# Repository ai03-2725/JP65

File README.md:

# JP65  
65%配列疑似JISキーボードPCB  
65% JIS-like hotswap keyboard PCB

Features  
- MITライセンスのもとでソース公開 / Open-source under the MIT license  
- Kailh製ソケットで全キーホットスワップ可能、はんだ付け無しで組み立て可能 / Fully hotswap  
- TADA68対応の65％ケースで使用可能 / Compatible with TADA68 standard cases  
- 一般的なキーサイズのみの日本語入力配列なので、GMKやePBTなどの標準キーキャップセットを使用可能 / Features a JIS-like key layout using standard keycap sizes   

[配列データ / Layout data](http://www.keyboard-layout-editor.com/#/gists/1bc89d661a44315f9f2ad37c4e321d41)  

Notes  
- 一番左下のネジ位置は一部分Winキーと重なってしまうので、ケースによっては入らない可能性があります。その場合はネジ無しでもOKです。/ The bottom-left screw might not fit due to collision against switches; if it does not, leave the screw uninstalled.  
- 左Winキー用スイッチの脚の一本はケース側スペーサーの位置と重なってしまうので、フラッシュカットなどで切る必要があります。One PCB-mount switch leg may need to be trimmed on the left Win key to fit; it is triple-circled on the silkscreen layer for identification.

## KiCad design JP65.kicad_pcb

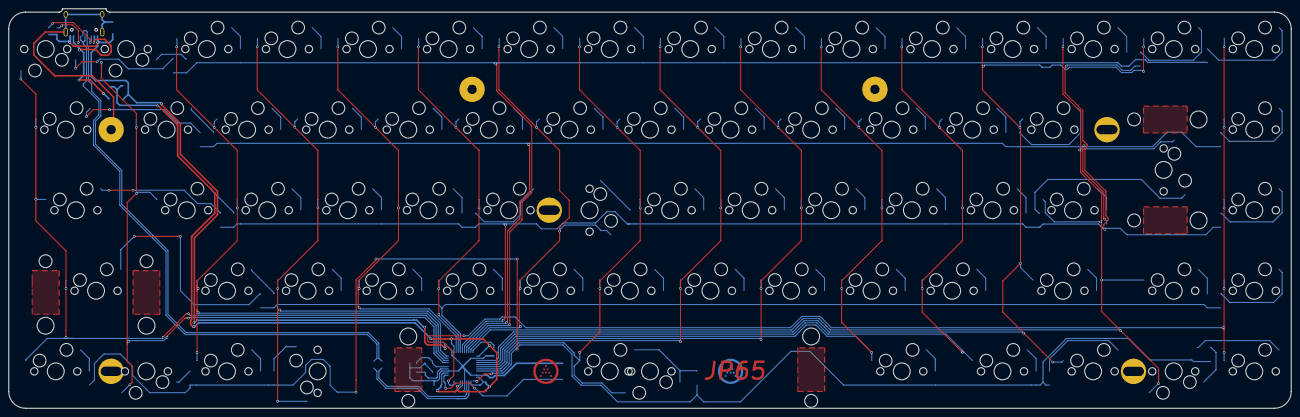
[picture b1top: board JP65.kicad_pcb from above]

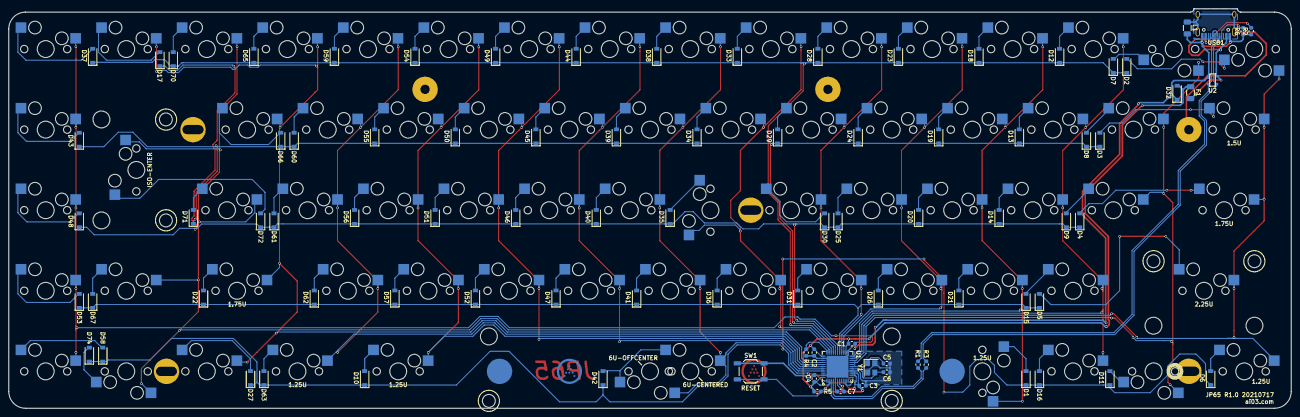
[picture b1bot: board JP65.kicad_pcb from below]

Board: 2 copper layers, 303.2 x 94.5 mm, 160 parts (90 on the bottom side), 104 nets.

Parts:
C1, C2, C3: 0.1uF; C_0603_1608Metric
C4: 10uF; C_0603_1608Metric
C5, C6: 22pF; C_0603_1608Metric
C7: 1uF; C_0603_1608Metric
D1, D2, D3, D4, D5, D6, D7, D8, D9, D10, D11, D12, D13, D14, D15, D16, D17, D18, D19, D20, D21, D22, D23, D24, D25, D26, D27, D28, D29, D30, D31, D33, D34, D35, D36, D37, D38, D39, D40, D41, D42, D43, D44, D45, D46, D47, D48, D49, D50, D51, D52, D53, D54, D55, D56, D57, D58, D59, D60, D61, D62, D63, D65, D66, D67, D70, D71, D72, D74: SOD-123; D_SOD-123
D32: SMF6.0CA; D_SOD-123
F1: Polyfuse_Small; Fuse_1206_3216Metric
K_#0_1, K_#1, K_#2, K_#3, K_#4, K_#5, K_#6, K_#7, K_#8, K_#9: MX-NoLED; MXOnly-1U-Hotswap
K_'1: MX-NoLED; MXOnly-1U-Hotswap
K_,1: MX-NoLED; MXOnly-1U-Hotswap
K_-1: MX-NoLED; MXOnly-1U-Hotswap
K_.1: MX-NoLED; MXOnly-1U-Hotswap
K_/1: MX-NoLED; MXOnly-1U-Hotswap
K_;1: MX-NoLED; MXOnly-1U-Hotswap
K_=1: MX-NoLED; MXOnly-1U-Hotswap
K_A1: MX-NoLED; MXOnly-1U-Hotswap
K_B1: MX-NoLED; MXOnly-1U-Hotswap
K_C1: MX-NoLED; MXOnly-1U-Hotswap
K_CAPS1: MX-LED; MXOnly-1.75U-Hotswap
K_D1: MX-NoLED; MXOnly-1U-Hotswap
K_DOWN1: MX-NoLED; MXOnly-1U-Hotswap
K_E1: MX-NoLED; MXOnly-1U-Hotswap
K_ENTER1: MX-NoLED; MXOnly-ISO-ROTATED-Hotswap
K_ESC1: MX-NoLED; MXOnly-1U-Hotswap
K_EX1, K_EX2, K_EX3, K_EX4: MX-NoLED; MXOnly-1U-Hotswap
K_F1: MX-NoLED; MXOnly-1U-Hotswap
K_G1: MX-NoLED; MXOnly-1U-Hotswap
K_H1: MX-NoLED; MXOnly-1U-Hotswap
K_I1: MX-NoLED; MXOnly-1U-Hotswap
K_J1: MX-NoLED; MXOnly-1U-Hotswap
K_K1: MX-NoLED; MXOnly-1U-Hotswap
K_L1: MX-NoLED; MXOnly-1U-Hotswap
K_LALT1: MX-NoLED; MXOnly-1U-Hotswap
K_LCTRL1: MX-NoLED; MXOnly-1.25U-Hotswap
K_LEFT1: MX-NoLED; MXOnly-1U-Hotswap
K_LGUI1: MX-NoLED; MXOnly-1U-Hotswap
K_LSFT1: MX-NoLED; MXOnly-2.25U-Hotswap
K_M1: MX-NoLED; MXOnly-1U-Hotswap
K_N1: MX-NoLED; MXOnly-1U-Hotswap
K_NFER1: MX-NoLED; MXOnly-1.25U-Hotswap
K_O1: MX-NoLED; MXOnly-1U-Hotswap
K_P1: MX-NoLED; MXOnly-1U-Hotswap
K_Q1: MX-NoLED; MXOnly-1U-Hotswap
K_R1: MX-NoLED; MXOnly-1U-Hotswap
K_RCTRL1: MX-NoLED; MXOnly-1.25U-Hotswap
K_RIGHT1: MX-NoLED; MXOnly-1U-Hotswap
K_RSFT1: MX-NoLED; MXOnly-1.75U-Hotswap
K_S1: MX-NoLED; MXOnly-1U-Hotswap
K_SBSPC1, K_SBSPC2: MX-NoLED; MXOnly-1U-Hotswap
K_SPC1: MX-NoLED; MXOnly-6U-Centered-Hotswap-ReversedStabilizers
K_SPC2: MX-NoLED; MXOnly-1U-Hotswap
K_T1: MX-NoLED; MXOnly-1U-Hotswap
K_TAB1: MX-NoLED; MXOnly-1.5U-Hotswap
K_U1: MX-NoLED; MXOnly-1U-Hotswap
K_UP1: MX-NoLED; MXOnly-1U-Hotswap
K_V1: MX-NoLED; MXOnly-1U-Hotswap
K_W1: MX-NoLED; MXOnly-1U-Hotswap
K_X1: MX-NoLED; MXOnly-1U-Hotswap
K_XFER1: MX-NoLED; MXOnly-1.25U-Hotswap
K_Y1: MX-NoLED; MXOnly-1U-Hotswap
K_Z1: MX-NoLED; MXOnly-1U-Hotswap
K_[1: MX-NoLED; MXOnly-1U-Hotswap
K_\1: MX-NoLED; MXOnly-1U-Hotswap
K_]1: MX-NoLED; MXOnly-1U-Hotswap
L1: 60R@100MHz; L_1206_3216Metric
R1, R3: 22; R_0603_1608Metric
R2, R6: 5.1k; R_0603_1608Metric
R4: 1k; R_0603_1608Metric
R5: 10k; R_0603_1608Metric
SW1: SW_Push; SW_SPST_TL3342
U1: ATmega32U4-MU; QFN-44-1EP_7x7mm_P0.5mm_EP5.2x5.2mm
U2: PRTR5V0U2X; SOT143B
USB1: HRO-TYPE-C-31-M-12; HRO-TYPE-C-31-M-12-Assembly
Y1: 16MHz; Crystal_SMD_3225-4Pin_3.2x2.5mm

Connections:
+5V: C1.1, C2.1, C3.1, C4.1, D32.2, F1.1, R5.2, U1.2, U1.7, U1.14, U1.24, U1.34, U1.44
COL0: K_CAPS1.1, K_ESC1.2, K_LCTRL1.1, K_LSFT1.1, K_TAB1.1, U1.20
COL1: K_#1.2, K_A1.1, K_LGUI1.2, K_Q1.1, U1.19
COL2: K_#2.1, K_LALT1.1, K_S1.1, K_W1.1, K_Z1.1, U1.21
COL3: K_#3.1, K_D1.1, K_E1.1, K_NFER1.1, K_X1.1, U1.22
COL4: K_#4.1, K_C1.1, K_F1.1, K_R1.1, U1.25
COL5: K_#5.1, K_G1.1, K_T1.1, K_V1.1, U1.26
COL6: K_#6.1, K_B1.1, K_H1.2, K_Y1.1, U1.31
COL7: K_#7.1, K_J1.1, K_N1.1, K_SPC1.1, K_SPC2.2, K_U1.1, U1.41
COL8: K_#8.1, K_I1.1, K_K1.1, K_M1.1, U1.40
COL9: K_#9.1, K_,1.1, K_L1.1, K_O1.1, U1.39
COL10: K_#0_1.1, K_.1.1, K_;1.1, K_P1.1, K_XFER1.1, U1.38
COL11: K_'1.1, K_-1.1, K_/1.1, K_RCTRL1.1, K_[1.1, U1.37
COL12: K_=1.1, K_LEFT1.1, K_RSFT1.1, K_SBSPC2.1, K_]1.1, U1.36
COL13: K_DOWN1.2, K_ENTER1.1, K_SBSPC1.1, K_UP1.1, K_\1.1, U1.32
COL14: K_EX1.1, K_EX2.1, K_EX3.1, K_EX4.1, K_RIGHT1.1, U1.10
D+: R1.2, U2.2, USB1.6, USB1.8
D-: R3.2, U2.3, USB1.5, USB1.7
Earth: L1.1, USB1.13
GND: C1.2, C2.2, C3.2, C4.2, C5.2, C6.2, C7.1, D32.1, L1.2, R2.1, R4.1, R6.1, SW1.1, U1.5, U1.15, U1.23, U1.35, U1.43, U1.45, U2.1, USB1.1, USB1.12, Y1.2, Y1.4
unnamed: C5.1, U1.17, Y1.1
unnamed: C6.1, U1.16, Y1.3
unnamed: C7.2, U1.6
unnamed: D1.2, K_NFER1.2
unnamed: D2.2, K_ESC1.1
unnamed: D3.2, K_TAB1.2
unnamed: D4.2, K_CAPS1.2
unnamed: D5.2, K_LSFT1.2
unnamed: D6.2, K_LCTRL1.2
unnamed: D7.2, K_#1.1
unnamed: D8.2, K_Q1.2
unnamed: D9.2, K_A1.2
unnamed: D10.2, K_XFER1.2
unnamed: D11.2, K_LGUI1.1
unnamed: D12.2, K_#2.2
unnamed: D13.2, K_W1.2
unnamed: D14.2, K_S1.2
unnamed: D15.2, K_Z1.2
unnamed: D16.2, K_LALT1.2
unnamed: D17.2, K_SBSPC2.2
unnamed: D18.2, K_#3.2
unnamed: D19.2, K_E1.2
unnamed: D20.2, K_D1.2
unnamed: D21.2, K_X1.2
unnamed: D22.2, K_RSFT1.2
unnamed: D23.2, K_#4.2
unnamed: D24.2, K_R1.2
unnamed: D25.2, K_F1.2
unnamed: D26.2, K_C1.2
unnamed: D27.2, K_LEFT1.2
unnamed: D28.2, K_#5.2
unnamed: D29.2, K_T1.2
unnamed: D30.2, K_G1.2
unnamed: D31.2, K_V1.2
unnamed: D33.2, K_#6.2
unnamed: D34.2, K_Y1.2
unnamed: D35.2, K_H1.1
unnamed: D36.2, K_B1.2
unnamed: D37.2, K_EX1.2
unnamed: D38.2, K_#7.2
unnamed: D39.2, K_U1.2
unnamed: D40.2, K_J1.2
unnamed: D41.2, K_N1.2
unnamed: D42.2, K_SPC1.2, K_SPC2.1
unnamed: D43.2, K_EX2.2
unnamed: D44.2, K_#8.2
unnamed: D45.2, K_I1.2
unnamed: D46.2, K_K1.2
unnamed: D47.2, K_M1.2
unnamed: D48.2, K_EX3.2
unnamed: D49.2, K_#9.2
unnamed: D50.2, K_O1.2
unnamed: D51.2, K_L1.2
unnamed: D52.2, K_,1.2
unnamed: D53.2, K_EX4.2
unnamed: D54.2, K_#0_1.2
unnamed: D55.2, K_P1.2
unnamed: D56.2, K_;1.2
unnamed: D57.2, K_.1.2
unnamed: D58.2, K_RIGHT1.2
unnamed: D59.2, K_-1.2
unnamed: D60.2, K_[1.2
unnamed: D61.2, K_'1.2
unnamed: D62.2, K_/1.2
unnamed: D63.2, K_RCTRL1.2
unnamed: D65.2, K_=1.2
unnamed: D66.2, K_]1.2
unnamed: D67.2, K_UP1.2
unnamed: D70.2, K_SBSPC1.2
unnamed: D71.2, K_\1.2
unnamed: D72.2, K_ENTER1.2
unnamed: D74.2, K_DOWN1.1
unnamed: R2.2, USB1.10
unnamed: R4.2, U1.33
unnamed: R5.1, SW1.2, U1.13
unnamed: R6.2, USB1.4
ROW0: D2.1, D7.1, D12.1, D18.1, D23.1, D28.1, D33.1, D37.1, D38.1, D44.1, D49.1, D54.1, D59.1, D65.1, D70.1, U1.30
ROW1: D3.1, D8.1, D13.1, D19.1, D24.1, D29.1, D34.1, D39.1, D43.1, D45.1, D50.1, D55.1, D60.1, D66.1, D71.1, U1.29
ROW2: D4.1, D9.1, D14.1, D17.1, D20.1, D25.1, D30.1, D35.1, D40.1, D46.1, D48.1, D51.1, D56.1, D61.1, D72.1, U1.28
ROW3: D5.1, D15.1, D21.1, D22.1, D26.1, D31.1, D36.1, D41.1, D47.1, D52.1, D53.1, D57.1, D62.1, D67.1, U1.27
ROW4: D1.1, D6.1, D10.1, D11.1, D16.1, D27.1, D42.1, D58.1, D63.1, D74.1, U1.1
USB+: R1.1, U1.4
USB-: R3.1, U1.3
VCC: F1.2, U2.4, USB1.2, USB1.11

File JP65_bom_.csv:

Component,Description,Part,References,Value,Footprint,Quantity Per PCB,Datasheet
1,"Unpolarized capacitor, small symbol",C_Small,C1 C2 C3,0.1uF,C_0603_1608Metric,3,~
2,"Unpolarized capacitor, small symbol",C_Small,C4,10uF,C_0603_1608Metric,1,~
3,"Unpolarized capacitor, small symbol",C_Small,C7,1uF,C_0603_1608Metric,1,~
4,"Unpolarized capacitor, small symbol",C_Small,C5 C6,22pF,C_0603_1608Metric,2,~
5,Bidirectional transient-voltage-suppression diode,D_TVS,D32,SMF6.0CA,D_SOD-123,1,~
6,"Diode, small symbol",D_Small,D1 D2 D3 D4 D5 D6 D7 D8 D9 D10 D11 D12 D13 D14 D15 D16 D17 D18 D19 D20 D21 D22 D23 D24 D25 D26 D27 D28 D29 D30 D31 D33 D34 D35 D36 D37 D38 D39 D40 D41 D42 D43 D44 D45 D46 D47 D48 D49 D50 D51 D52 D53 D54 D55 D56 D57 D58 D59 D60 D61 D62 D63 D65 D66 D67 D70 D71 D72 D74,SOD-123,D_SOD-123,69,~
7,"Resettable fuse, polymeric positive temperature coefficient, small symbol",Polyfuse_Small,F1,Polyfuse_Small,Fuse_1206_3216Metric,1,~
8,Kailh Hotswap Socket,MX-NoLED,K_CAPS1,MX-LED,MXOnly-1.75U-Hotswap,1,
9,Kailh Hotswap Socket,MX-NoLED,"K_#0_1 K_#1 K_#2 K_#3 K_#4 K_#5 K_#6 K_#7 K_#8 K_#9 K_'1 K_,1 K_-1 K_.1 K_/1 K_;1 K_=1 K_A1 K_B1 K_C1 K_D1 K_DOWN1 K_E1 K_ESC1 K_EX1 K_EX2 K_EX3 K_EX4 K_F1 K_G1 K_H1 K_I1 K_J1 K_K1 K_L1 K_LALT1 K_LEFT1 K_LGUI1 K_M1 K_N1 K_O1 K_P1 K_Q1 K_R1 K_RIGHT1 K_S1 K_SBSPC1 K_SBSPC2 K_SPC2 K_T1 K_U1 K_UP1 K_V1 K_W1 K_X1 K_Y1 K_Z1 K_[1 K_\1 K_]1",MX-NoLED,MXOnly-1U-Hotswap,60,
10,Kailh Hotswap Socket,MX-NoLED,K_ENTER1,MX-NoLED,MXOnly-ISO-ROTATED-Hotswap,1,
11,Kailh Hotswap Socket,MX-NoLED,K_LCTRL1 K_NFER1 K_RCTRL1 K_XFER1,MX-NoLED,MXOnly-1.25U-Hotswap,4,
12,Kailh Hotswap Socket,MX-NoLED,K_LSFT1,MX-NoLED,MXOnly-2.25U-Hotswap,1,
13,Kailh Hotswap Socket,MX-NoLED,K_RSFT1,MX-NoLED,MXOnly-1.75U-Hotswap,1,
14,Kailh Hotswap Socket,MX-NoLED,K_SPC1,MX-NoLED,MXOnly-6U-Centered-Hotswap-ReversedStabilizers,1,
15,Kailh Hotswap Socket,MX-NoLED,K_TAB1,MX-NoLED,MXOnly-1.5U-Hotswap,1,
16,"Inductor with ferrite core, small symbol",L_Core_Ferrite_Small,L1,60R@100MHz,L_1206_3216Metric,1,~
17,"Resistor, small symbol",R_Small,R5,10k,R_0603_1608Metric,1,~
18,"Resistor, small symbol",R_Small,R4,1k,R_0603_1608Metric,1,~
19,"Resistor, small symbol",R_Small,R1 R3,22,R_0603_1608Metric,2,~
20,"Resistor, small symbol",R_Small,R2 R6,5.1k,R_0603_1608Metric,2,~
21,"Push button switch, generic, two pins",SW_Push,SW1,SW_Push,SW_SPST_TL3342,1,~
22,"16MHz, 16kB Flash, 1.25kB SRAM, 512B EEPROM, USB 2.0, QFN-44",ATmega32U4-MU,U1,ATmega32U4-MU,QFN-44-1EP_7x7mm_P0.5mm_EP5.2x5.2mm,1,http://ww1.microchip.com/downloads/en/DeviceDoc/Atmel-7766-8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
23,ESD Protection IC,PRTR5V0U2X,U2,PRTR5V0U2X,SOT143B,1,
24,USB Connector,HRO-TYPE-C-31-M-12,USB1,HRO-TYPE-C-31-M-12,HRO-TYPE-C-31-M-12-Assembly,1,
25,"Four pin crystal, GND on pins 2 and 4, small symbol",Crystal_GND24_Small,Y1,16MHz,Crystal_SMD_3225-4Pin_3.2x2.5mm,1,~
,,,,,,,
,,,,,,,
,,,,,,,
,,,,,,,
,,,,,,,
Component Groups:,25,,,,,,
Component Count:,160,,,,,,
Fitted Components:,160,,,,,,
Number of PCBs:,1,,,,,,
Total components:,160,,,,,,
Schematic Version:,,,,,,,
Schematic Date:,,,,,,,
BoM Date:,7/20/2021 11:29:49 PM,,,,,,
Schematic Source:,C:\Users\ai03\Documents\GitHub\JIS65\JP65.sch,,,,,,
KiCad Version:,Eeschema (5.1.4)-1,,,,,,

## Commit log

2021-07-17 Clone JP60 files to begin
2021-07-17 Make PCB
2021-07-17 Add gerber zip
2021-07-17 Add plate files
2021-07-17 Add rudimentary ja translation
2021-07-20 Update BOM
2021-08-07 Update plate files
2023-04-18 Repair plate ISO enter stabilizer orientation
